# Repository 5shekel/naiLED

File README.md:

naiLED
======

a mempixel on a finger nail sized board
this board is meant to go on a fingernail, collect color info<br>
store it in memory and reflect it back using an RGB LED.<br>

MCU - AVR ATtiny85 <br>
EEPROM - 24LC16bt (16Kb) <br>
RGB LED - generic <br>
color sensor (digital) - TCSL3414 <br>

<br>

<br><br>

contact >  yair99 [at] gmail<br>

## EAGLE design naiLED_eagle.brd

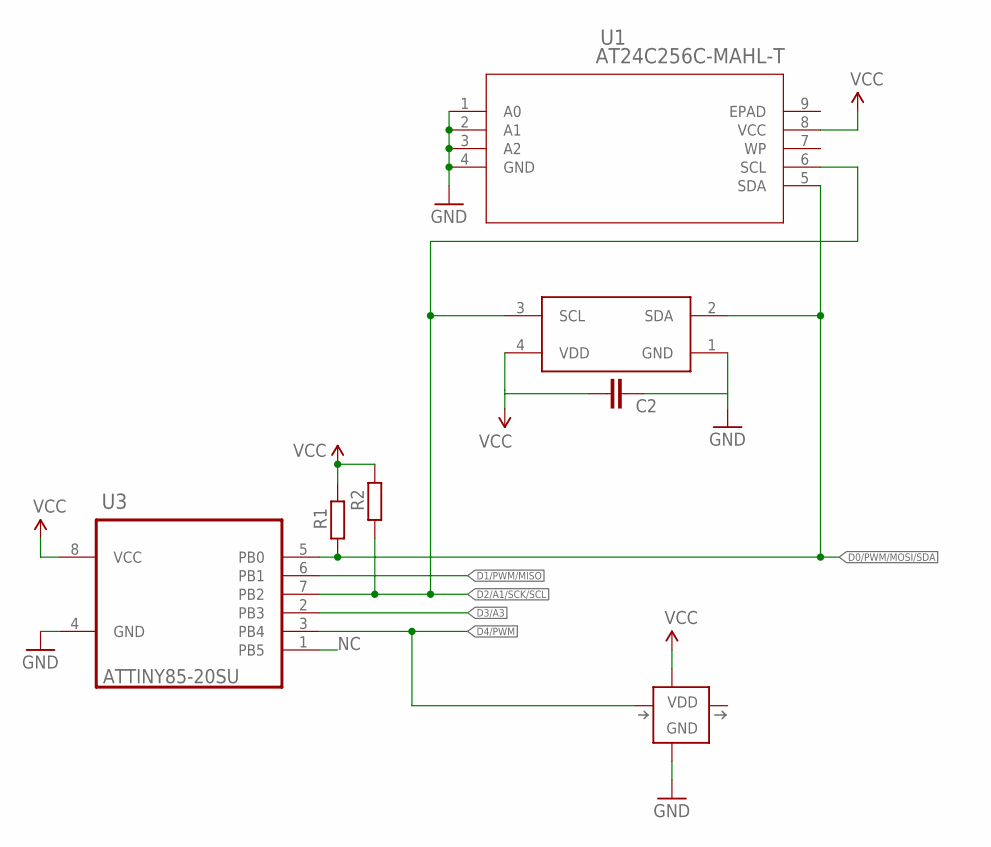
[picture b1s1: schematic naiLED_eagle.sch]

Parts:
C2: CAPACITOR_NPOL-0402; C402
R1, R2: RESISTOR-0402; R402
U1: AT24C256C-MAHL-T; 8MA2
U3: ATTINY85-20SU; SOIC127P798X216-8N
U$1: SK6812MINI; LED-3535
U$2: VEML6040; 4-TFLGA

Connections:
D0/PWM/MOSI/SDA: R1.1, U1.5 (SDA), U3.5 (PB0), U$2.2 (SDA)
D1/PWM/MISO: U3.6 (PB1)
D2/A1/SCK/SCL: R2.1, U1.6 (SCL), U3.7 (PB2), U$2.3 (SCL)
D3/A3: U3.2 (PB3)
D4/PWM: U3.3 (PB4), U$1.2 (DI)
GND: C2.1, U1.1 (A0), U1.2 (A1), U1.3 (A2), U1.4 (GND), U3.4 (GND), U$1.1 (GND), U$2.1 (GND)
NC: U3.1 (PB5)
VCC: C2.2, R1.2, R2.2, U1.8 (VCC), U3.8 (VCC), U$1.3 (VDD), U$2.4 (VDD)

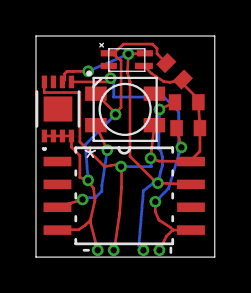
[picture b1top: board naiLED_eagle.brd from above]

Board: 2 copper layers, 9.9 x 12.3 mm, 8 parts (1 on the bottom side), 5 nets.

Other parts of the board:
E$1: OSHW_FILLX100_NOTEXT

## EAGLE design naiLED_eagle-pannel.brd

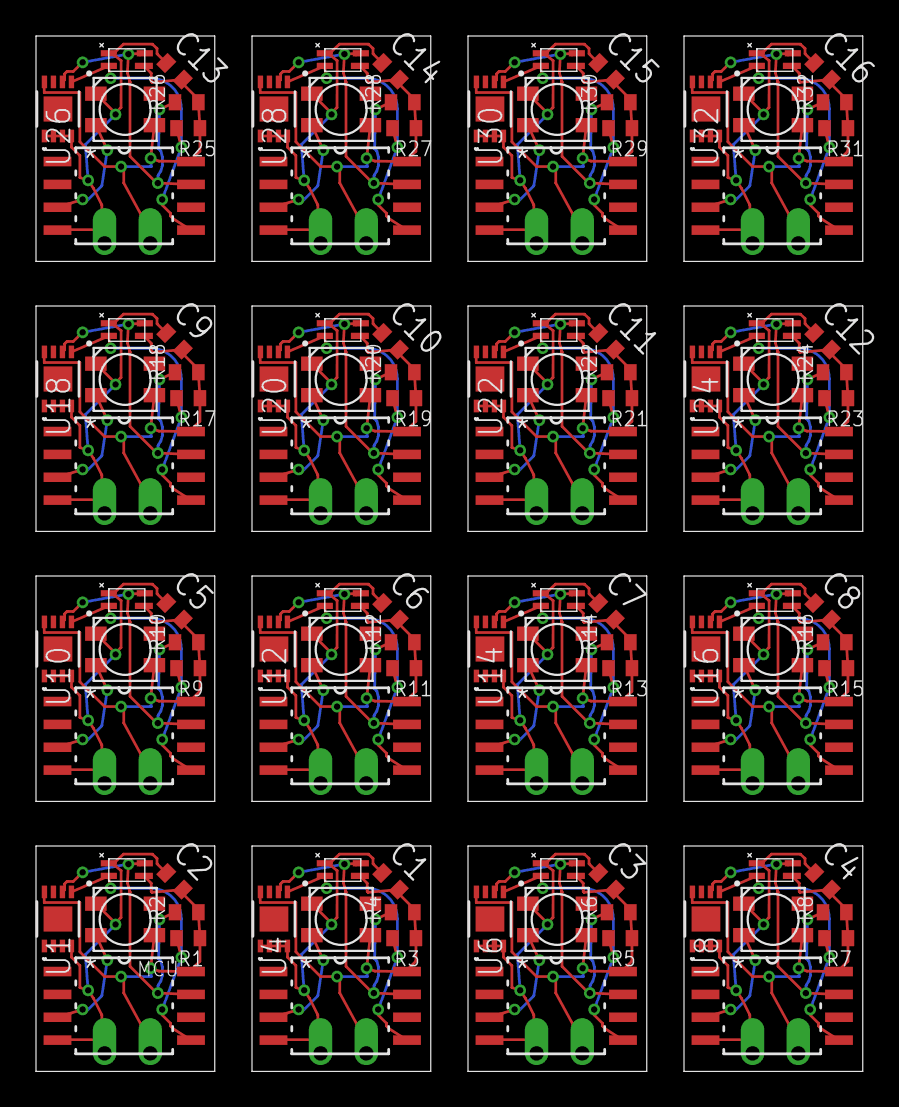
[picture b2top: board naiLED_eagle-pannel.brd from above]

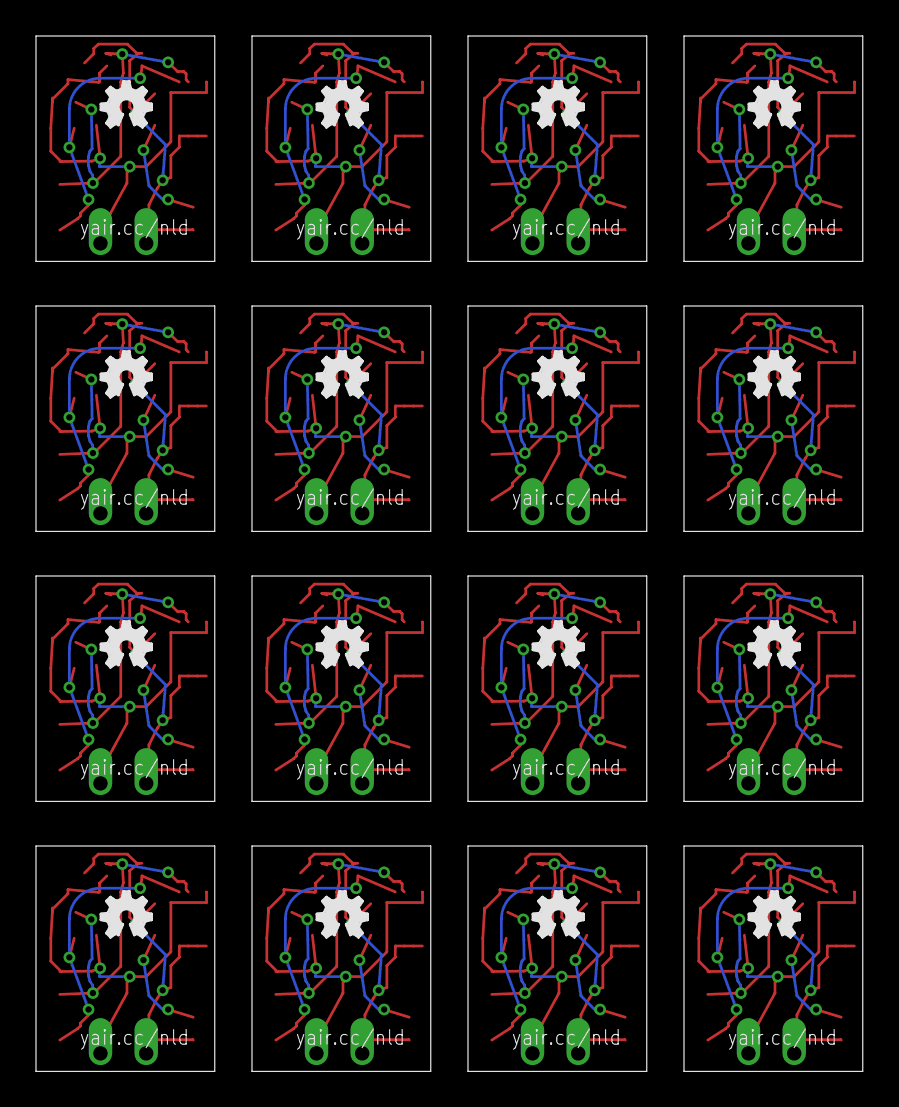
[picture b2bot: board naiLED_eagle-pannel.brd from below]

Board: 2 copper layers, 45.9 x 57.5 mm, 160 parts (16 on the bottom side), 80 nets.

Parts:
C1, C2, C3, C4, C5, C6, C7, C8, C9, C10, C11, C12, C13, C14, C15, C16: C402
E$1, E$2, E$3, E$4, E$5, E$6, E$7, E$8, E$9, E$10, E$11, E$12, E$13, E$14, E$15, E$16: OSHW_FILLX100_NOTEXT
R1, R2, R3, R4, R5, R6, R7, R8, R9, R10, R11, R12, R13, R14, R15, R16, R17, R18, R19, R20, R21, R22, R23, R24, R25, R26, R27, R28, R29, R30, R31, R32: R402
U1, U4, U6, U8, U10, U12, U14, U16, U18, U20, U22, U24, U26, U28, U30, U32: AT24C256C-MAHL-T; 8MA2
U2, U3, U5, U7, U9, U11, U13, U15, U17, U19, U21, U23, U25, U27, U29, U31: ATTINY85-20SU; SOIC127P798X216-8N
U$1, U$4, U$7, U$10, U$13, U$16, U$19, U$22, U$25, U$28, U$31, U$34, U$37, U$40, U$43, U$46: SK6812MINI; LED-3535
U$2, U$5, U$8, U$11, U$14, U$17, U$20, U$23, U$26, U$29, U$32, U$35, U$38, U$41, U$44, U$47: VEML6040; 4-TFLGA
U$3, U$6, U$9, U$12, U$15, U$18, U$21, U$24, U$27, U$30, U$33, U$36, U$39, U$42, U$45, U$48: HEADER-1X1; 1X1_LONG
VCC, VCC1, VCC2, VCC3, VCC4, VCC5, VCC6, VCC7, VCC8, VCC9, VCC10, VCC11, VCC12, VCC13, VCC14, VCC15: HEADER-1X1; 1X1_LONG

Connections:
D0/PWM/MOSI/SDA: R1.1, U1.5, U3.5, U$2.2
D0/PWM/MOSI/SDA1: R3.1, U2.5, U4.5, U$5.2
D0/PWM/MOSI/SDA2: R5.1, U5.5, U6.5, U$8.2
D0/PWM/MOSI/SDA3: R7.1, U7.5, U8.5, U$11.2
D0/PWM/MOSI/SDA4: R9.1, U9.5, U10.5, U$14.2
D0/PWM/MOSI/SDA5: R11.1, U11.5, U12.5, U$17.2
D0/PWM/MOSI/SDA6: R13.1, U13.5, U14.5, U$20.2
D0/PWM/MOSI/SDA7: R15.1, U15.5, U16.5, U$23.2
D0/PWM/MOSI/SDA8: R17.1, U17.5, U18.5, U$26.2
D0/PWM/MOSI/SDA9: R19.1, U19.5, U20.5, U$29.2
D0/PWM/MOSI/SDA10: R21.1, U21.5, U22.5, U$32.2
D0/PWM/MOSI/SDA11: R23.1, U23.5, U24.5, U$35.2
D0/PWM/MOSI/SDA12: R25.1, U25.5, U26.5, U$38.2
D0/PWM/MOSI/SDA13: R27.1, U27.5, U28.5, U$41.2
D0/PWM/MOSI/SDA14: R29.1, U29.5, U30.5, U$44.2
D0/PWM/MOSI/SDA15: R31.1, U31.5, U32.5, U$47.2
D2/A1/SCK/SCL: R2.1, U1.6, U3.7, U$2.3
D2/A1/SCK/SCL1: R4.1, U2.7, U4.6, U$5.3
D2/A1/SCK/SCL2: R6.1, U5.7, U6.6, U$8.3
D2/A1/SCK/SCL3: R8.1, U7.7, U8.6, U$11.3
D2/A1/SCK/SCL4: R10.1, U9.7, U10.6, U$14.3
D2/A1/SCK/SCL5: R12.1, U11.7, U12.6, U$17.3
D2/A1/SCK/SCL6: R14.1, U13.7, U14.6, U$20.3
D2/A1/SCK/SCL7: R16.1, U15.7, U16.6, U$23.3
D2/A1/SCK/SCL8: R18.1, U17.7, U18.6, U$26.3
D2/A1/SCK/SCL9: R20.1, U19.7, U20.6, U$29.3
D2/A1/SCK/SCL10: R22.1, U21.7, U22.6, U$32.3
D2/A1/SCK/SCL11: R24.1, U23.7, U24.6, U$35.3
D2/A1/SCK/SCL12: R26.1, U25.7, U26.6, U$38.3
D2/A1/SCK/SCL13: R28.1, U27.7, U28.6, U$41.3
D2/A1/SCK/SCL14: R30.1, U29.7, U30.6, U$44.3
D2/A1/SCK/SCL15: R32.1, U31.7, U32.6, U$47.3
D4/PWM: U3.3, U$1.2
D4/PWM1: U2.3, U$4.2
D4/PWM2: U5.3, U$7.2
D4/PWM3: U7.3, U$10.2
D4/PWM4: U9.3, U$13.2
D4/PWM5: U11.3, U$16.2
D4/PWM6: U13.3, U$19.2
D4/PWM7: U15.3, U$22.2
D4/PWM8: U17.3, U$25.2
D4/PWM9: U19.3, U$28.2
D4/PWM10: U21.3, U$31.2
D4/PWM11: U23.3, U$34.2
D4/PWM12: U25.3, U$37.2
D4/PWM13: U27.3, U$40.2
D4/PWM14: U29.3, U$43.2
D4/PWM15: U31.3, U$46.2
GND: C2.1, U1.1, U1.2, U1.3, U1.4, U3.4, U$1.1, U$2.1, U$3.P$1
GND1: C1.1, U2.4, U4.1, U4.2, U4.3, U4.4, U$4.1, U$5.1, U$6.P$1
GND2: C3.1, U5.4, U6.1, U6.2, U6.3, U6.4, U$7.1, U$8.1, U$9.P$1
GND3: C4.1, U7.4, U8.1, U8.2, U8.3, U8.4, U$10.1, U$11.1, U$12.P$1
GND4: C5.1, U9.4, U10.1, U10.2, U10.3, U10.4, U$13.1, U$14.1, U$15.P$1
GND5: C6.1, U11.4, U12.1, U12.2, U12.3, U12.4, U$16.1, U$17.1, U$18.P$1
GND6: C7.1, U13.4, U14.1, U14.2, U14.3, U14.4, U$19.1, U$20.1, U$21.P$1
GND7: C8.1, U15.4, U16.1, U16.2, U16.3, U16.4, U$22.1, U$23.1, U$24.P$1
GND8: C9.1, U17.4, U18.1, U18.2, U18.3, U18.4, U$25.1, U$26.1, U$27.P$1
GND9: C10.1, U19.4, U20.1, U20.2, U20.3, U20.4, U$28.1, U$29.1, U$30.P$1
GND10: C11.1, U21.4, U22.1, U22.2, U22.3, U22.4, U$31.1, U$32.1, U$33.P$1
GND11: C12.1, U23.4, U24.1, U24.2, U24.3, U24.4, U$34.1, U$35.1, U$36.P$1
GND12: C13.1, U25.4, U26.1, U26.2, U26.3, U26.4, U$37.1, U$38.1, U$39.P$1
GND13: C14.1, U27.4, U28.1, U28.2, U28.3, U28.4, U$40.1, U$41.1, U$42.P$1
GND14: C15.1, U29.4, U30.1, U30.2, U30.3, U30.4, U$43.1, U$44.1, U$45.P$1
GND15: C16.1, U31.4, U32.1, U32.2, U32.3, U32.4, U$46.1, U$47.1, U$48.P$1
VCC: C2.2, R1.2, R2.2, U1.8, U3.8, U$1.3, U$2.4, VCC.P$1
VCC1: C1.2, R3.2, R4.2, U2.8, U4.8, U$4.3, U$5.4, VCC1.P$1
VCC2: C3.2, R5.2, R6.2, U5.8, U6.8, U$7.3, U$8.4, VCC2.P$1
VCC3: C4.2, R7.2, R8.2, U7.8, U8.8, U$10.3, U$11.4, VCC3.P$1
VCC4: C5.2, R9.2, R10.2, U9.8, U10.8, U$13.3, U$14.4, VCC4.P$1
VCC5: C6.2, R11.2, R12.2, U11.8, U12.8, U$16.3, U$17.4, VCC5.P$1
VCC6: C7.2, R13.2, R14.2, U13.8, U14.8, U$19.3, U$20.4, VCC6.P$1
VCC7: C8.2, R15.2, R16.2, U15.8, U16.8, U$22.3, U$23.4, VCC7.P$1
VCC8: C9.2, R17.2, R18.2, U17.8, U18.8, U$25.3, U$26.4, VCC8.P$1
VCC9: C10.2, R19.2, R20.2, U19.8, U20.8, U$28.3, U$29.4, VCC9.P$1
VCC10: C11.2, R21.2, R22.2, U21.8, U22.8, U$31.3, U$32.4, VCC10.P$1
VCC11: C12.2, R23.2, R24.2, U23.8, U24.8, U$34.3, U$35.4, VCC11.P$1
VCC12: C13.2, R25.2, R26.2, U25.8, U26.8, U$37.3, U$38.4, VCC12.P$1
VCC13: C14.2, R27.2, R28.2, U27.8, U28.8, U$40.3, U$41.4, VCC13.P$1
VCC14: C15.2, R29.2, R30.2, U29.8, U30.8, U$43.3, U$44.4, VCC14.P$1
VCC15: C16.2, R31.2, R32.2, U31.8, U32.8, U$46.3, U$47.4, VCC15.P$1

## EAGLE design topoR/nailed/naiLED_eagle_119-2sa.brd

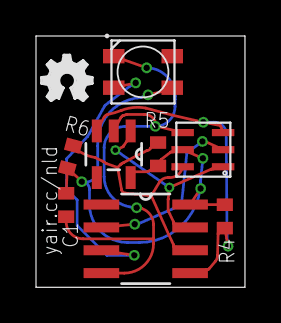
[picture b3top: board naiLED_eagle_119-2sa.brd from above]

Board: 2 copper layers, 11.6 x 14.0 mm, 9 parts (0 on the bottom side), 7 nets.

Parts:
C1: C402
E$1: OSHW_FILLX100_NOTEXT
IC1: TCS3414; DFN-6PIN
R4, R5, R6: R402
U2: SOT95P290X145-5N
U3: SOIC127P600X175-8N
U$1: SK6812MINI; LED-3535

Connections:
D0/PWM/MOSI/SDA: IC1.P$3, R4.1, U2.3, U3.5
D1/PWM/MISO: IC1.P$4, R5.1, R6.2, U3.6
D2/A1/SCK/SCL: IC1.P$1, U2.1, U3.7
D3/A3: IC1.P$2, U3.2
D4/PWM: U3.3, U$1.2
GND: C1.2, IC1.P$6, U2.2, U3.4, U$1.1
VCC: C1.1, IC1.P$5, R4.2, R5.2, R6.1, U2.5, U3.8, U$1.3

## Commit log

2014-03-20 Create naiLED_eagle.sch
    eagle file for schematics
2014-03-20 Create naiLED_eagle.brd
    board design, TBD
2014-03-21 Update naiLED_eagle.brd
    board layout design by florin lazar
2014-03-21 Update README.md
    added pics and stuff
2014-12-17 added library
    ripup all , changed LED to CLPP4 and added resistors
2014-12-17 working on the at841
2014-12-18 some changes, not major
2014-12-18 some changes, nothing major
2017-07-09 width 6mil
2017-07-09 miniSK led
2017-07-09 topoR
2017-07-09 changed attiny25 footprint to 85, ripup
2017-07-09 routing mid
2017-07-09 more vias
2017-07-10 sent to fab, single board
2017-07-10 ripup all, added vias to attiny
2017-07-10 library and changed to attiny85 foo\tprint..
2017-07-11 mem docs
2017-07-11 new memory
2017-07-11 layout, meh
2017-07-12 lol reflow
2017-07-12 auditing
2023-04-23 websafe color
